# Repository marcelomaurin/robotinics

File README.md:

# Robotinics

[Português](README.md) · [English](README_EN.md) · [Español](README_ES.md)

Robotinics é uma plataforma aberta de robótica, automação e experimentação criada para integrar **mecânica, eletrônica, firmware, computação embarcada e software** em um mesmo projeto.

O objetivo não é oferecer apenas um robô pronto, mas uma base evolutiva para estudo, prototipagem e desenvolvimento de novas funcionalidades.

## Origem do projeto

O Robotinics nasceu em **2015** como **Trabalho de Conclusão de Curso (TCC)** do curso de **Técnico em Mecânica Industrial**, apresentado na **Etec José Martimiano da Silva**, em Ribeirão Preto/SP, unidade do **Centro Paula Souza**.

Esse contexto explica a natureza multidisciplinar do projeto desde sua origem: o trabalho não foi concebido apenas como software ou eletrônica, mas como um sistema integrado envolvendo **mecânica, fabricação de peças, eletrônica, acionamentos, sensores, microcontroladores e software**.

A partir do trabalho acadêmico original, o Robotinics continuou evoluindo como plataforma experimental, incorporando novas revisões mecânicas, placas eletrônicas, Arduino, Raspberry Pi, visão computacional e outros módulos de software.

Instituição: [Etec José Martimiano da Silva – Centro Paula Souza](https://www.cps.sp.gov.br/etecs/etec-jose-martimiano-da-silva/)

## Visão geral

O projeto reúne:

- estrutura mecânica e peças para fabricação e impressão 3D;
- projetos de placas eletrônicas e distribuição de alimentação;
- Arduino Mega como controlador principal de baixo nível;
- módulo de cabeça baseado em Arduino Nano;
- sensores, servomotores, motores, laser apontador e ultrassom;
- integração com Raspberry Pi;
- banco de dados e interface web;
- documentação didática e material histórico do projeto.

## Arquitetura

```text
                      Raspberry Pi
                 visão / software / lógica
                           │
                           │ serial
                           ▼
                     Arduino Mega
                controle físico principal
                  /        │         \
             motores    sensores    servos
                           │
                           ▼
                    MCabeca / Nano
                ┌──────────┼──────────┐
              Servo X    Servo Y    Ultrassom
                           │
                       Laser / LEDs
```

O Raspberry Pi fica responsável por processamento de mais alto nível. O Arduino Mega concentra a maior quantidade de I/O e executa o controle físico. O MCabeca é um módulo especializado da cabeça robótica.

## Módulos

| Módulo | Conteúdo |
|---|---|
| [Eletrônica](Eletronic/README.md) | esquemas, placas, alimentação e PCBs |
| [Mecânica](Mecanic/README.md) | SolidWorks, STL e peças estruturais |
| [Software](Software/README.md) | firmware, Raspberry, banco e interface |
| [Arduino](Software/arduino/README.md) | firmwares embarcados |
| [Mega](Software/arduino/robotinics/README.md) | controlador principal do robô |
| [MCabeca](Software/arduino/MCabeca/README.md) | cabeça ativa: servos, laser, LEDs e ultrassom |
| [Raspberry](Software/raspberry/README.md) | processamento de alto nível e I/O |
| [Robotinics AI](docs/ai/README.md) | TCHATGPT, internet, RAG, visão, agentes e documentação assistida |
| [Imagem Yocto](Software/raspberry/yocto/README.md) | Linux reproduzível para Raspberry Pi 4/5 |
| [Database](Software/database/README.md) | estrutura de dados do projeto |
| [Site](Software/site/README.md) | interface web histórica |
| [Documentação](docs/README.md) | manuais e material de referência |

## MCabeca e percepção ativa

O MCabeca possui dois servos associados a um **apontador laser**, LEDs e sensor ultrassônico. A intenção do módulo não é atuar como arma: o laser funciona como referência óptica e apontador visual.

Associado a uma câmera controlada pelo Raspberry Pi, o módulo pode ser usado para:

- apontamento visual;
- varredura angular;
- identificação do ponto laser na imagem;
- auxílio à estimativa de profundidade de uma câmera monocular;
- scanning de uma região;
- combinação de distância visual e ultrassônica;
- acompanhamento experimental de objetos.

A calibração visual pertence ao Raspberry Pi. O microcontrolador deve apenas receber e executar ângulos e comandos físicos.

## Continuação com IA no Raspberry Pi

A continuidade da Rev. 3 propõe o Raspberry Pi como **computador de bordo inteligente**, usando a biblioteca [TCHATGPT](https://github.com/marcelomaurin/CHATGPT) para integrar LLM, agentes, RAG, visão, voz e acesso controlado à internet.

A arquitetura preserva o princípio de segurança do projeto: a IA interpreta, pesquisa e planeja; o Arduino Mega continua responsável pelo controle físico determinístico.

Documentação: [docs/ai/README.md](docs/ai/README.md)

Para agentes de IA que precisem compreender ou atualizar este repositório, consulte também [AGENTS.md](AGENTS.md) e [AI_README.md](AI_README.md).

## Imagem Linux do Raspberry Pi

A continuidade do projeto possui uma camada Yocto própria em [Software/raspberry/yocto/README.md](Software/raspberry/yocto/README.md). Ela cria uma imagem reproduzível para Raspberry Pi 4/5 com gateway serial, rede, voz/visão opcionais e preparação para o runtime TCHATGPT ARM64.

## Firmware

O projeto possui dois firmwares principais:

### Arduino Mega

Local: [Software/arduino/robotinics](Software/arduino/robotinics)

Responsável por controle do robô, motores, servos, sensores, comunicação e segurança básica.

### Arduino Nano — MCabeca

Local: [Software/arduino/MCabeca](Software/arduino/MCabeca)

Responsável pelo módulo de cabeça robótica.

Os firmwares estão passando por uma modernização mantendo compatibilidade com o hardware e o protocolo legado:

- PR #3 — refatoração do firmware do Mega;
- PR #4 — otimização do MCabeca para Arduino Nano.

## Estrutura do repositório

```text
robotinics/
├── Eletronic/
│   ├── arduino/
│   ├── eagle/
│   ├── pcb/
│   └── pcb wizzard/
├── Mecanic/
│   ├── solidwork/
│   └── stl/
├── Software/
│   ├── arduino/
│   │   ├── robotinics/
│   │   └── MCabeca/
│   ├── database/
│   ├── raspberry/
│   │   └── yocto/
│   └── site/
└── docs/
```

## Robotinics Rev. 4

A evolução atual do projeto está organizada na [Robotinics Rev. 4](docs/rev4/README.md), que formaliza a arquitetura em camadas, o roadmap de modernização, a preservação do protocolo legado e os critérios de validação para firmware, Gateway, simulador, IA e distribuição.

A Rev. 4 é incremental: o hardware atual continua sendo a base do projeto e cada mudança estrutural deve ser validada antes de substituir comportamento existente.

## Documentação histórica

O repositório mantém o material completo produzido ao longo da evolução do projeto, inclusive o manual **Projetos IoT com Arduino e Raspberry**.

Consulte [docs/README.md](docs/README.md).

## Filosofia do projeto

Robotinics foi concebido como uma plataforma multidisciplinar. A evolução do projeto deve preservar quatro princípios:

1. hardware reproduzível;
2. módulos independentes;
3. protocolo compatível entre dispositivos;
4. separação entre controle físico e processamento de alto nível.

## Autor

**Marcelo Maurin Martins**

- GitHub: [marcelomaurin](https://github.com/marcelomaurin)
- Site: [Maurinsoft](https://maurinsoft.com.br)

---

Robotinics é um projeto experimental e educacional. Ao trabalhar com motores, alimentação elétrica, laser, baterias ou partes móveis, utilize procedimentos adequados de segurança.

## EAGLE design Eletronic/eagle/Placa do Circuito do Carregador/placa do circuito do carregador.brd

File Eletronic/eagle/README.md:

# Projetos EAGLE

[Eletrônica](../README.md) · [English](README.en.md) · [Español](README.es.md)

Este diretório contém projetos eletrônicos criados no Autodesk EAGLE.

## Conteúdo

Há projetos relacionados a:

- controle de servomotor;
- LEDs;
- circuito de carregamento;
- distribuição de 5 V.

## Uso

Antes de fabricar uma placa:

1. confirme a revisão;
2. verifique alimentação e corrente;
3. compare a pinagem com o firmware;
4. confira disponibilidade dos componentes;
5. revise trilhas de potência.

Os arquivos refletem diferentes momentos do projeto e devem ser validados antes de uso.

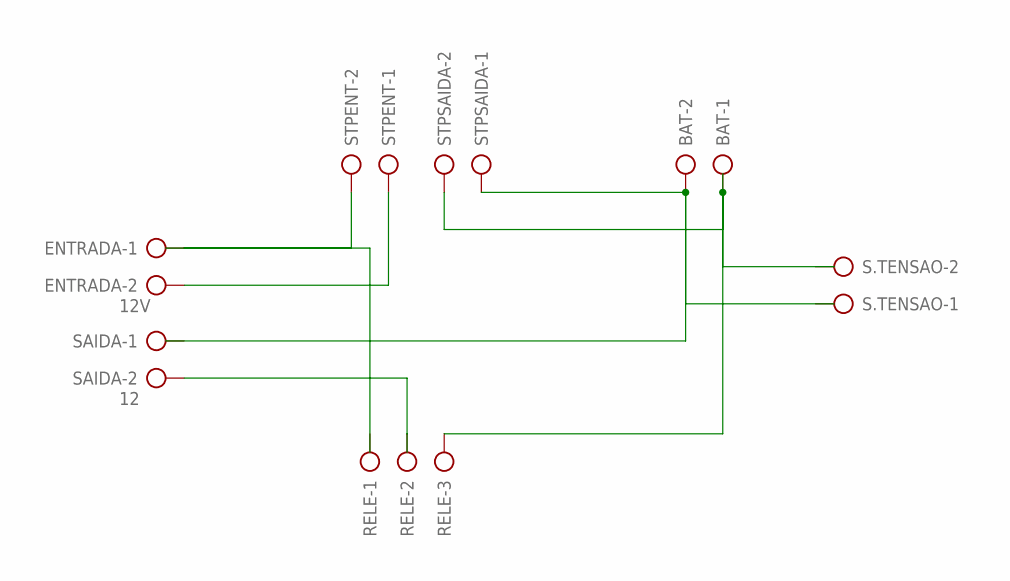
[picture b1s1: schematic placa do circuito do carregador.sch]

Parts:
BAT: AK300/2
ENTRADA: 12V; AK300/2
RELE: AK500/3-H
S.TENSAO: AK300/2
SAIDA: 12; AK300/2
STPENT: AK300/2
STPSAIDA: AK300/2

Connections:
unnamed: ENTRADA.1, STPENT.2
unnamed: BAT.2, STPSAIDA.1
unnamed: ENTRADA.2, STPENT.1
unnamed: BAT.1, RELE.3, STPSAIDA.2

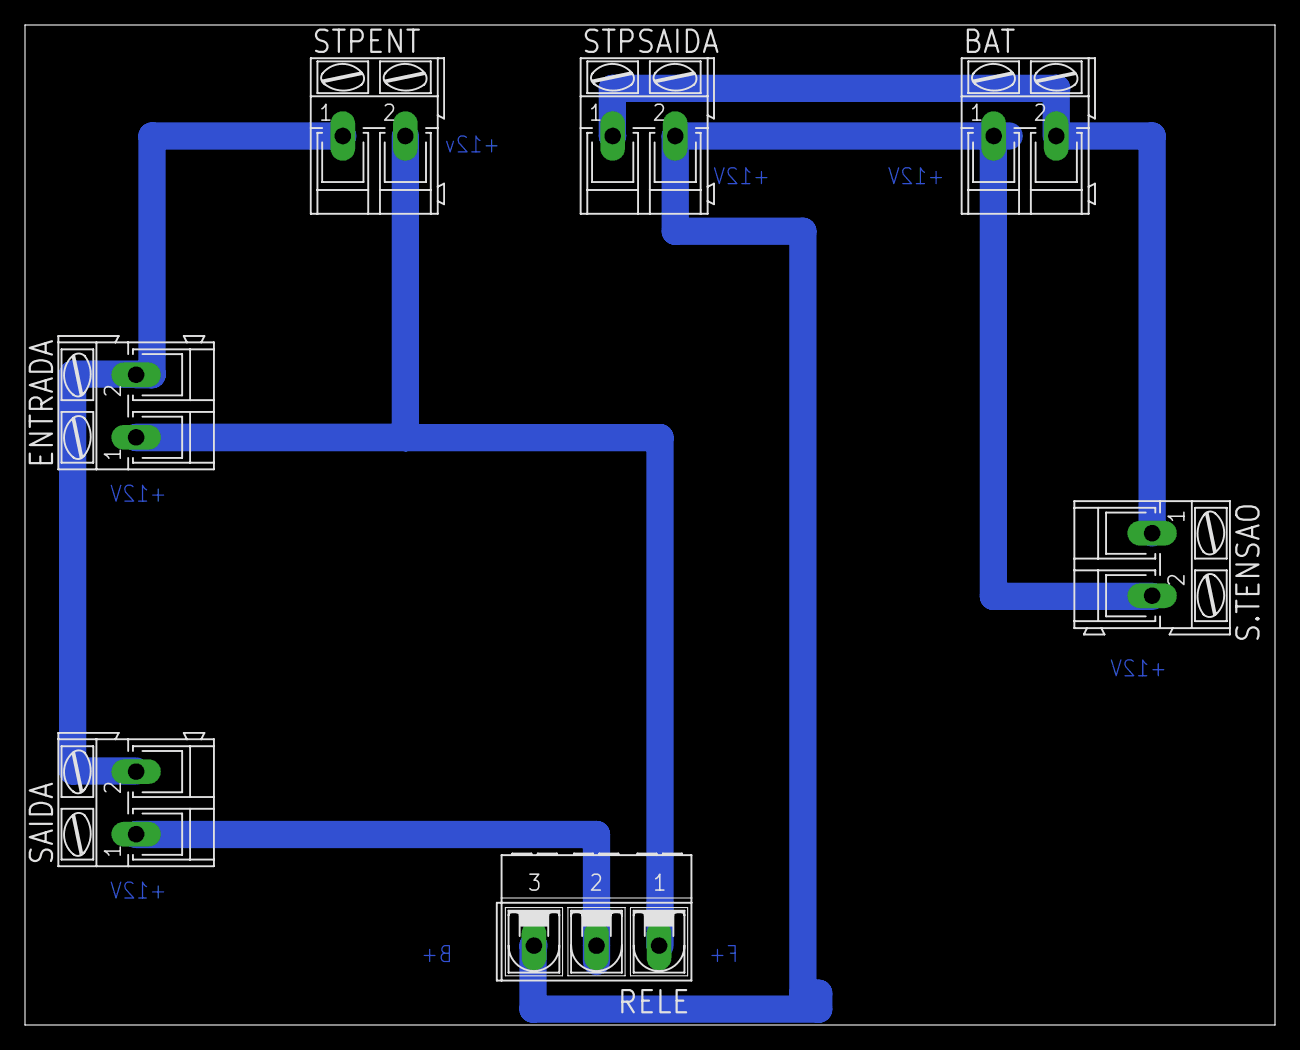
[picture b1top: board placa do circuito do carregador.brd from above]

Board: 2 copper layers, 100.0 x 80.0 mm, 7 parts (0 on the bottom side), 4 nets.

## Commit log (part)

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2021-04-06 Lançamento do Robotinics
2021-04-06 manual
2021-04-06 projeto robotinics
2021-04-06 correcao
2022-08-02 mudanca
2022-08-02 mudancas
